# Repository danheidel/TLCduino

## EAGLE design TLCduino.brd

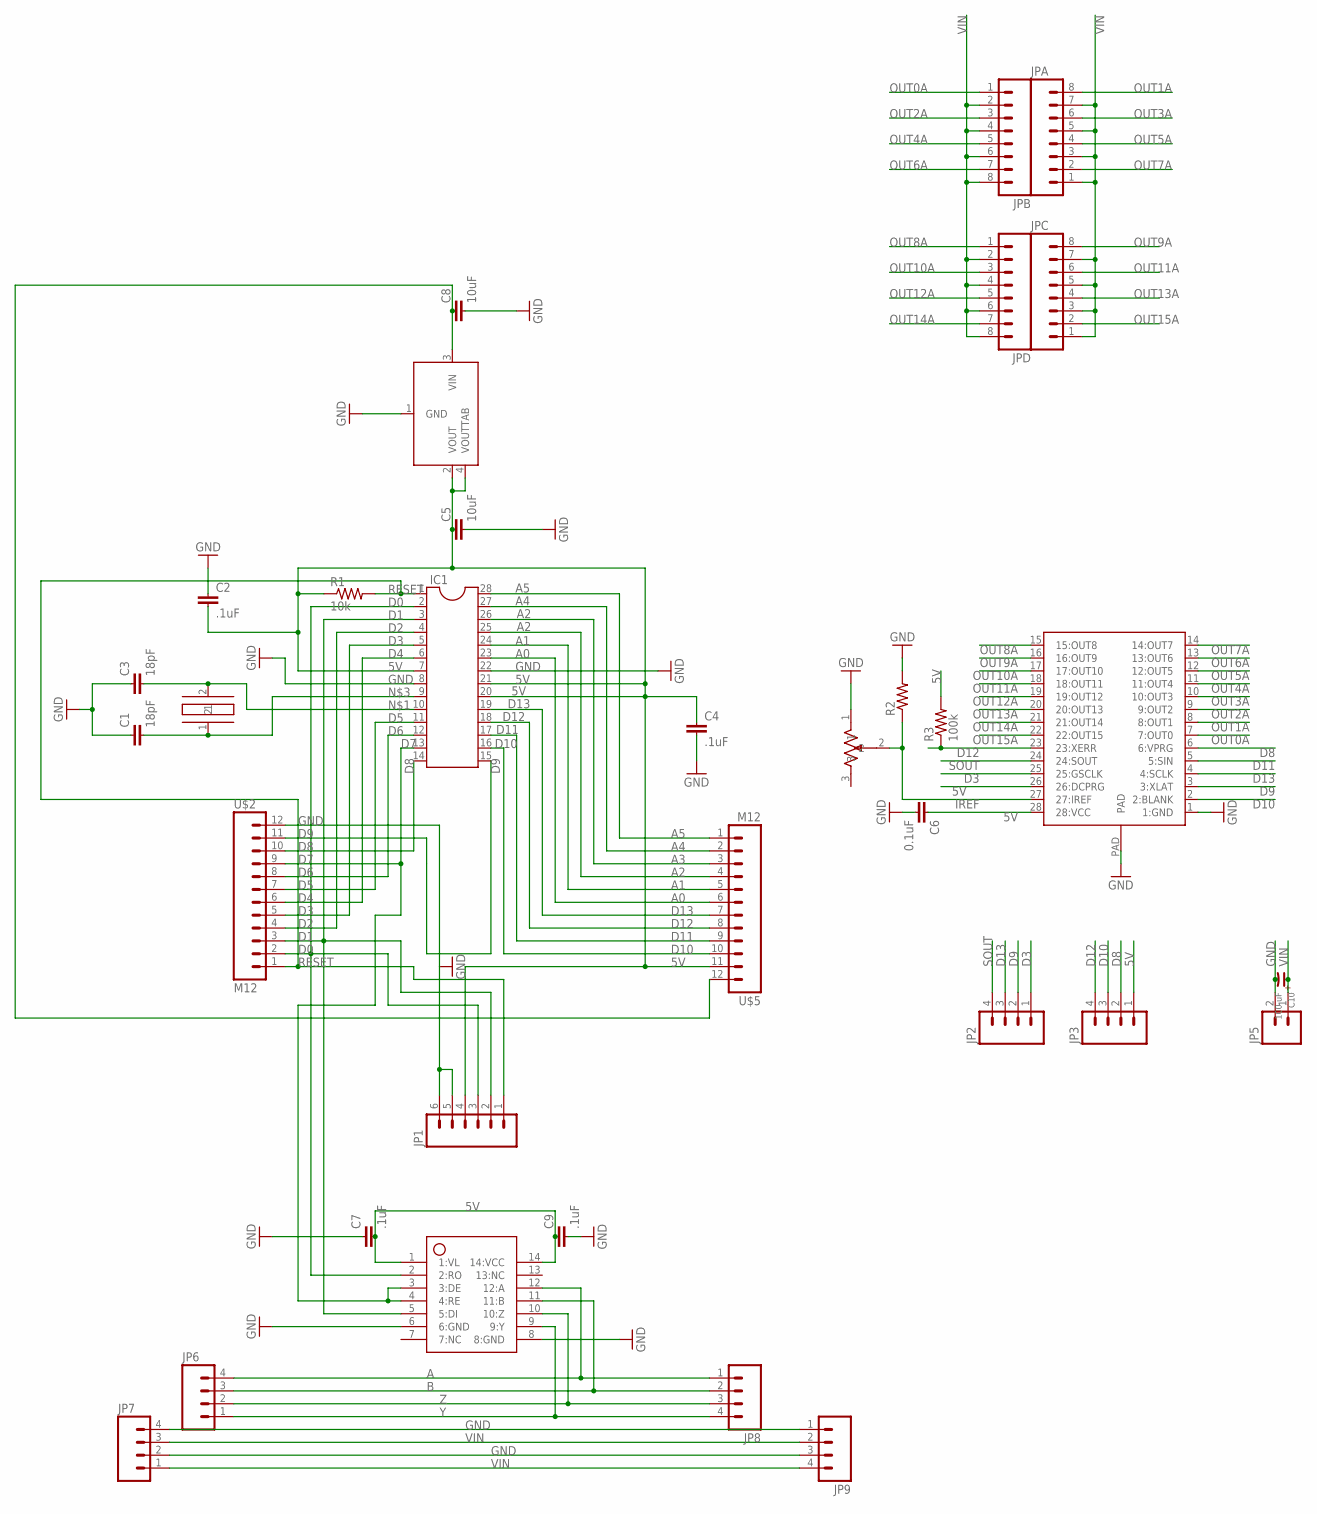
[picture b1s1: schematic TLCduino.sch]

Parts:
5V: ZLDO1117
C1, C3: 18pF; 0603-CAP
C2, C4, C7, C9: .1uF; 0805
C5, C8: 10uF; 1206
C6: 0.1uF; 0805
C10: 100 uF; 5X11MMCAP
IC1: DIL28-3
JP1: M06LOCK; 1X06_LOCK
JP2, JP3, JP6, JP7, JP8, JP9: M04LOCK; 1X04_LOCK
JP5: M02LOCK; 1X02_LOCK
JPA: M08LOCK; 1X08_LOCK
JPB: M08LOCK; 1X08_LOCK
JPC: M08LOCK; 1X08_LOCK
JPD: M08LOCK; 1X08_LOCK
R1: 10k; 0805
R2: RESISTOR; 0805
R3: 100k; 0805
U$1: HC49US
U$2, U$5: M12; 1X12_LOCK
U$3: TLC5940; HTSSOP-28
U$4: TRIMPOTTC33X-2; TC33X-2
U$6: MAX13432; SO14

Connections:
5V: 5V.2 (VOUT), 5V.4 (VOUTTAB), C2.2, C4.1, C5.1, C6.1, C7.2, C9.1, IC1.7, IC1.20, IC1.21, JP1.4, JP3.1, R1.1, R3.2, U$3.26 (26:DCPRG), U$3.28 (28:VCC), U$5.11, U$6.1 (1:VL), U$6.14 (14:VCC)
A: JP6.4, JP8.1, U$6.12 (12:A)
A0: IC1.23, U$5.6
A1: IC1.24, U$5.5
A2: IC1.25, U$5.4
A3: IC1.26, U$5.3
A4: IC1.27, U$5.2
A5: IC1.28, U$5.1
B: JP6.3, JP8.2, U$6.11 (11:B)
D0: IC1.2, JP1.3, U$2.2, U$6.2 (2:RO)
D1: IC1.3, JP1.2, U$2.3, U$6.5 (5:DI)
D2: IC1.4, U$2.4
D3: IC1.5, JP2.1, U$2.5, U$3.25 (25:GSCLK)
D4: IC1.6, U$2.6
D5: IC1.11, U$2.7
D6: IC1.12, U$2.8
D7: IC1.13, U$2.9, U$6.3 (3:DE), U$6.4 (4:RE)
D8: IC1.14, JP3.2, U$2.10, U$3.6 (6:VPRG)
D9: IC1.15, JP2.2, U$2.11, U$3.3 (3:XLAT)
D10: IC1.16, JP3.3, U$3.2 (2:BLANK), U$5.10
D11: IC1.17, U$3.5 (5:SIN), U$5.9
D12: IC1.18, JP3.4, R3.1, U$3.23 (23:XERR), U$5.8
D13: IC1.19, JP2.3, U$3.4 (4:SCLK), U$5.7
GND: 5V.1 (GND), C1.1, C2.1, C3.1, C4.2, C5.2, C6.2, C7.1, C8.2, C9.2, C10.-, IC1.8, IC1.22, JP1.5, JP1.6, JP5.2, JP7.2, JP7.4, JP9.1, JP9.3, R2.2, U$2.12, U$3.1 (1:GND), U$3.PAD, U$4.1, U$6.6 (6:GND), U$6.8 (8:GND)
IREF: R2.1, U$3.27 (27:IREF), U$4.2
unnamed: C3.2, IC1.10, U$1.2
unnamed: C1.2, IC1.9, U$1.1
OUT0A: JPB.1, U$3.7 (7:OUT0)
OUT1A: JPA.8, U$3.8 (8:OUT1)
OUT2A: JPB.3, U$3.9 (9:OUT2)
OUT3A: JPA.6, U$3.10 (10:OUT3)
OUT4A: JPB.5, U$3.11 (11:OUT4)
OUT5A: JPA.4, U$3.12 (12:OUT5)
OUT6A: JPB.7, U$3.13 (13:OUT6)
OUT7A: JPA.2, U$3.14 (14:OUT7)
OUT8A: JPD.1, U$3.15 (15:OUT8)
OUT9A: JPC.8, U$3.16 (16:OUT9)
OUT10A: JPD.3, U$3.17 (17:OUT10)
OUT11A: JPC.6, U$3.18 (18:OUT11)
OUT12A: JPD.5, U$3.19 (19:OUT12)
OUT13A: JPC.4, U$3.20 (20:OUT13)
OUT14A: JPD.7, U$3.21 (21:OUT14)
OUT15A: JPC.2, U$3.22 (22:OUT15)
RESET: IC1.1, JP1.1, R1.2, U$2.1
SOUT: JP2.4, U$3.24 (24:SOUT)
VIN: 5V.3 (VIN), C8.1, C10.+, JP5.1, JP7.1, JP7.3, JP9.2, JP9.4, JPA.1, JPA.3, JPA.5, JPA.7, JPB.2, JPB.4, JPB.6, JPB.8, JPC.1, JPC.3, JPC.5, JPC.7, JPD.2, JPD.4, JPD.6, JPD.8, U$5.12
Y: JP6.1, JP8.4, U$6.9 (9:Y)
Z: JP6.2, JP8.3, U$6.10 (10:Z)

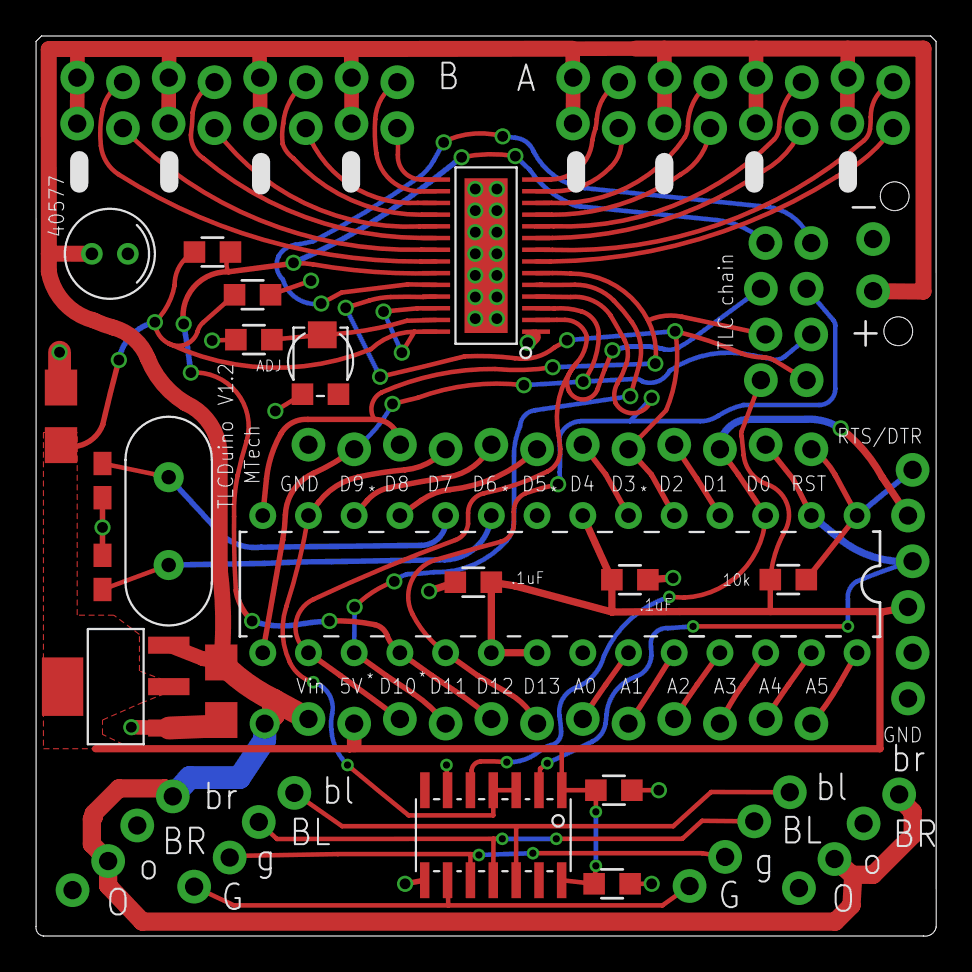
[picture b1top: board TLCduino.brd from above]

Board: 2 copper layers, 50.0 x 50.0 mm, 33 parts (0 on the bottom side), 48 nets.

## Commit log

2011-11-08 minor edits
2011-11-11 minor edits zip file for bare bones 2-layer
2011-11-22 Fixes on the EEPROM/register pin. Improved ground plane. Version sent on 2nd board run.
2011-12-01 Added soldermask hole under TLC5940, increased PS poly spacing, remade and zipped CAM files.
2011-12-01 Outline and paste files.
2011-12-16 Major revision, added RS-485 communication, redid the output pin ordering, more silkscreen, large filter cap and other minor tweaks.
2011-12-24 File clean up. -Removed Eagle backup files. -Removed old .zip files.
2012-03-05 Major revision, on board jacks, other revisions to address weaknesses discovered in actual use.
2012-03-16 update cream EPS file for the older boards.
2012-03-16 new .eps files
2012-03-17 Fixed errors in .eps files.
2012-03-25 A few more .eps tweaks
2012-04-26 minor tweaks
